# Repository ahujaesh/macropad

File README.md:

note: this has been approved and this repository archived

# e'sPad

Screenshot of overall pad with top transparent

Screenshot of pad without transparency of top case

Screenshot of schematic

Screenshot of PCB

Screenshot of bottom Case

Screenshot of top case

|Bill of materials:|Notes|
|-|-|
|PCB||
|top and bottom Case|I have my own 3d printer and can print the case myself if that's easier|
|6 switches||
|6 keycaps|I have my own 3d printer and can print the keycaps myself if that's easier|
|1 potentiometer/knob|I have my own potentiometer and can use that if you dont want to send me one|
|XIAO rp2040 seed studio||
Note: I have my own soldering iron as well btw so i can use that

Sorry if i missed anything

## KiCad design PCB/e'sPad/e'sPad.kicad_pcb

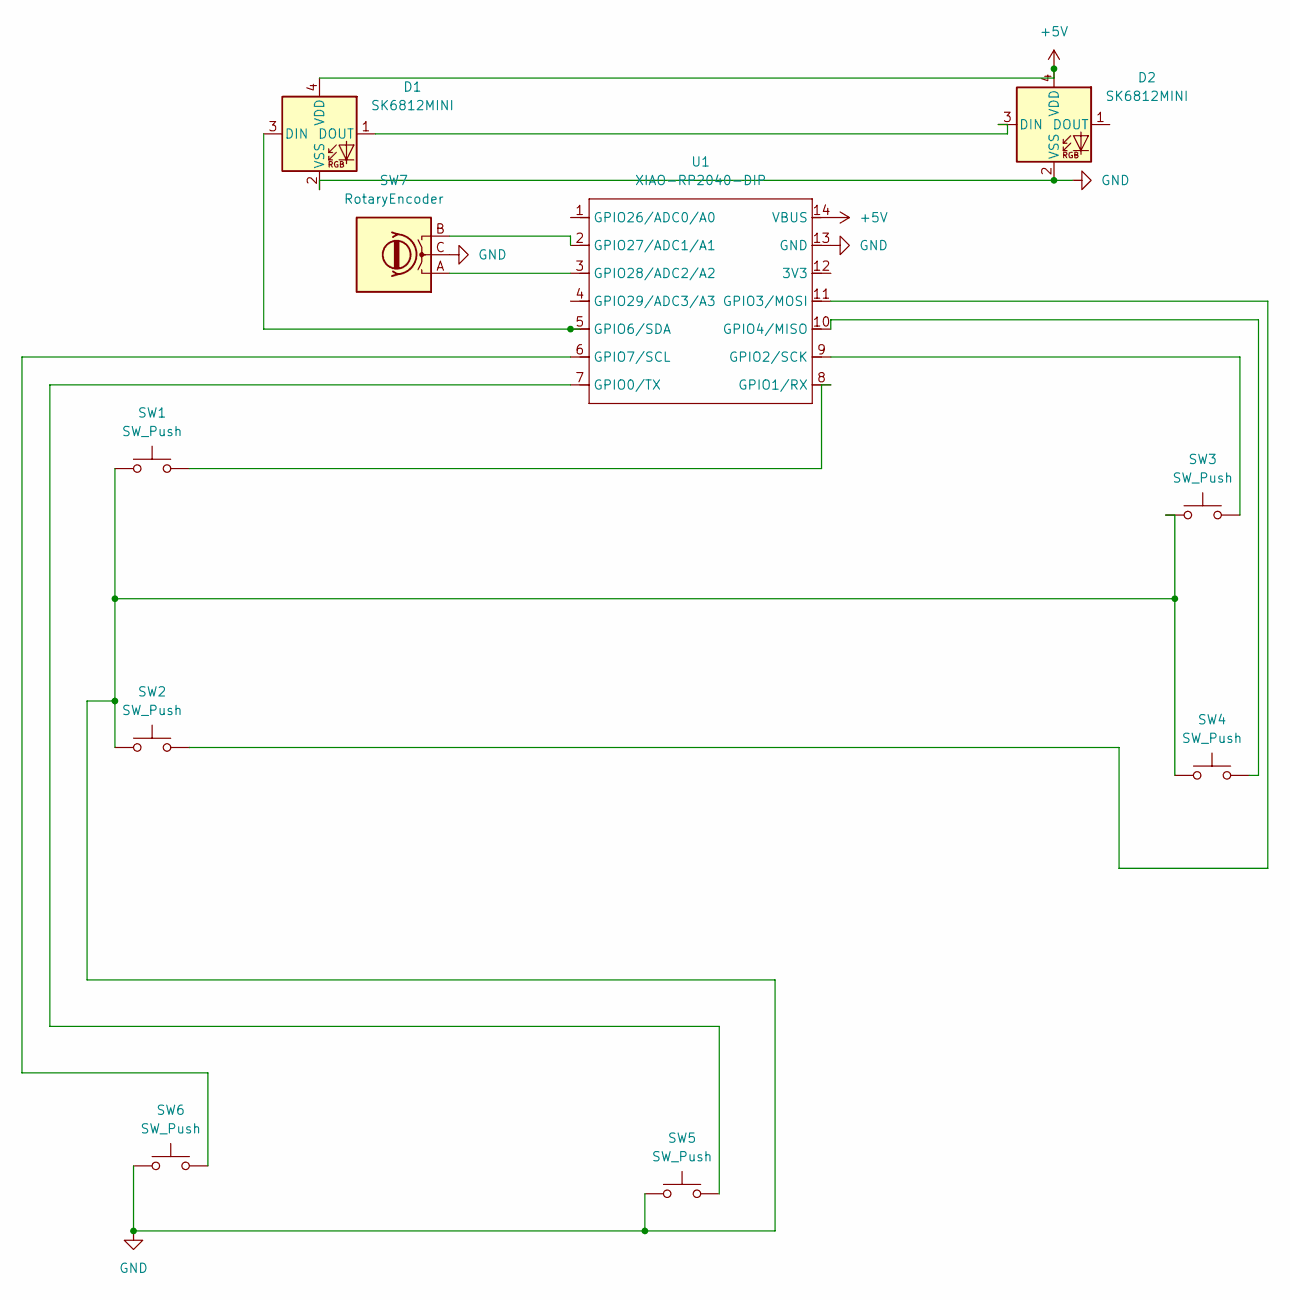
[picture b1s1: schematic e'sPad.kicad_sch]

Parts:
D1, D2: SK6812MINI; LED_SK6812MINI_PLCC4_3.5x3.5mm_P1.75mm
SW1, SW2, SW3, SW4, SW5, SW6: SW_Push; SW_Cherry_MX_1.00u_PCB
SW7: RotaryEncoder; RotaryEncoder_Alps_EC11E_Vertical_H20mm
U1: XIAO-RP2040-DIP

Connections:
+5V: D1.4 (VDD), D2.4 (VDD), U1.14 (VBUS)
GND: D1.2 (VSS), D2.2 (VSS), SW1.1, SW2.1, SW3.1, SW4.1, SW5.1, SW6.1, SW7.C, U1.13 (GND)
unnamed: D1.3 (DIN), U1.5 (GPIO6/SDA)
unnamed: D1.1 (DOUT), D2.3 (DIN)
unnamed: SW5.2, U1.7 (GPIO0/TX)
unnamed: SW1.2, U1.8 (GPIO1/RX)
unnamed: SW3.2, U1.9 (GPIO2/SCK)
unnamed: SW2.2, U1.11 (GPIO3/MOSI)
unnamed: SW4.2, U1.10 (GPIO4/MISO)
unnamed: SW6.2, U1.6 (GPIO7/SCL)
unnamed: SW7.B, U1.2 (GPIO27/ADC1/A1)
unnamed: SW7.A, U1.3 (GPIO28/ADC2/A2)

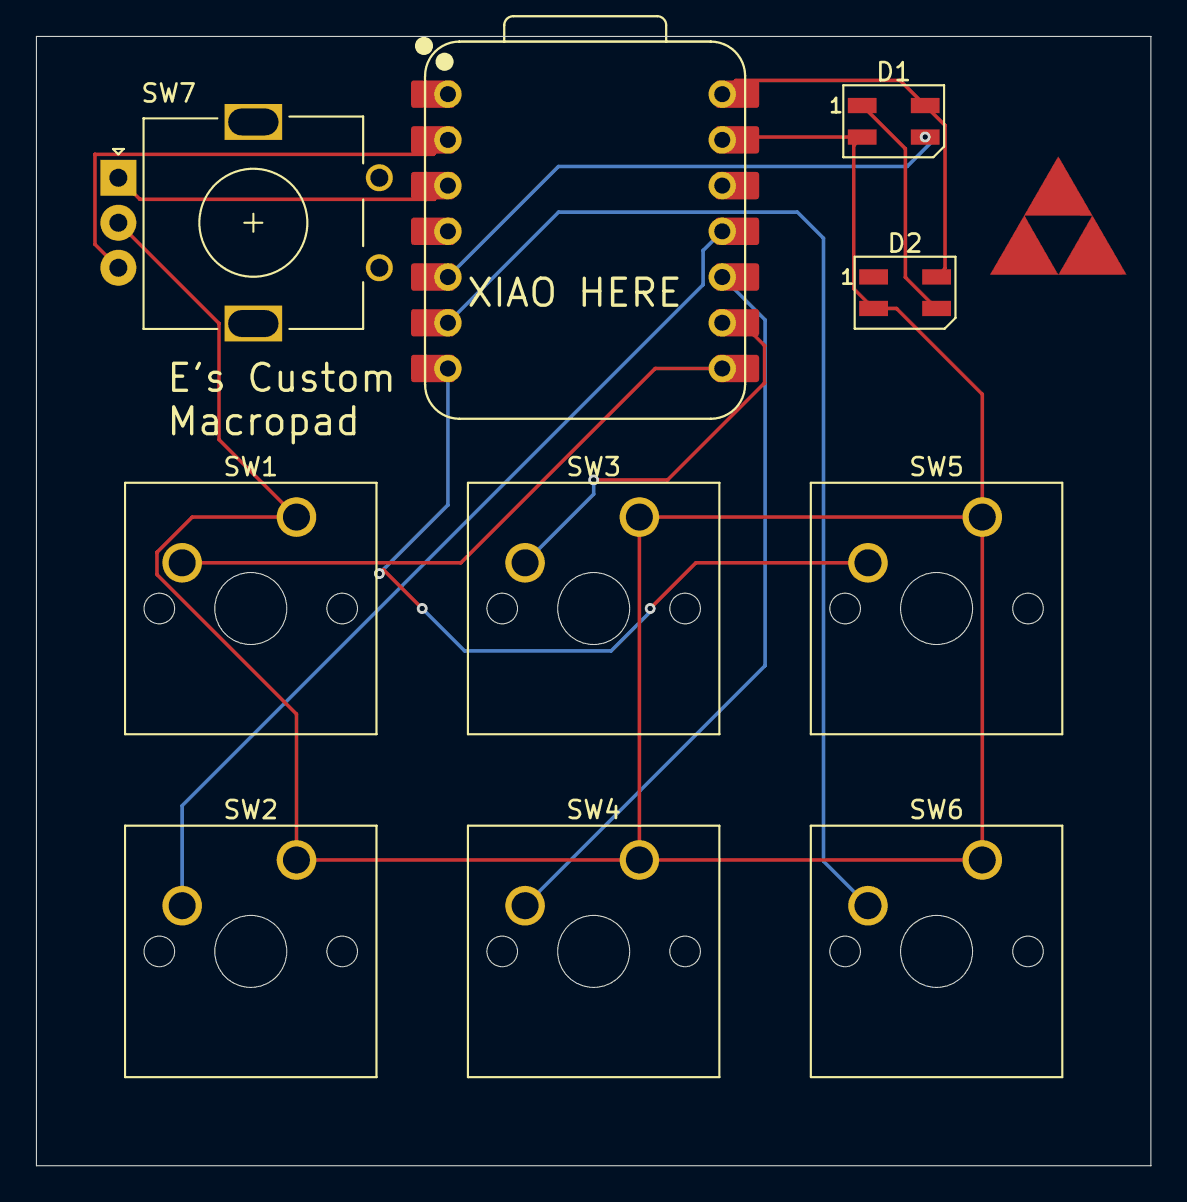
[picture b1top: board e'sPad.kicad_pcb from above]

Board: 2 copper layers, 61.9 x 62.7 mm, 10 parts (0 on the bottom side), 12 nets.

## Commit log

2025-06-22 finished pcb scematic and started main pcb
2025-06-23 finished v1
2025-06-23 sone things didnt commit properly last time its all there now
2025-06-25 fixed it
2025-06-25 remove outdated comment
    (I was going to leave it without a top shell but I added one so the comment is now out of date)
2025-06-25 Rename complete_cad.step to outdated_complete_cad.step
    the new complete cad is in the production folder
2025-06-25 updated formatting of the BOM
2025-06-26 Onshape mobile allowed for the final edit and the project will be approved
2025-06-28 added JLC pcb invoice
2025-07-18 it works now
